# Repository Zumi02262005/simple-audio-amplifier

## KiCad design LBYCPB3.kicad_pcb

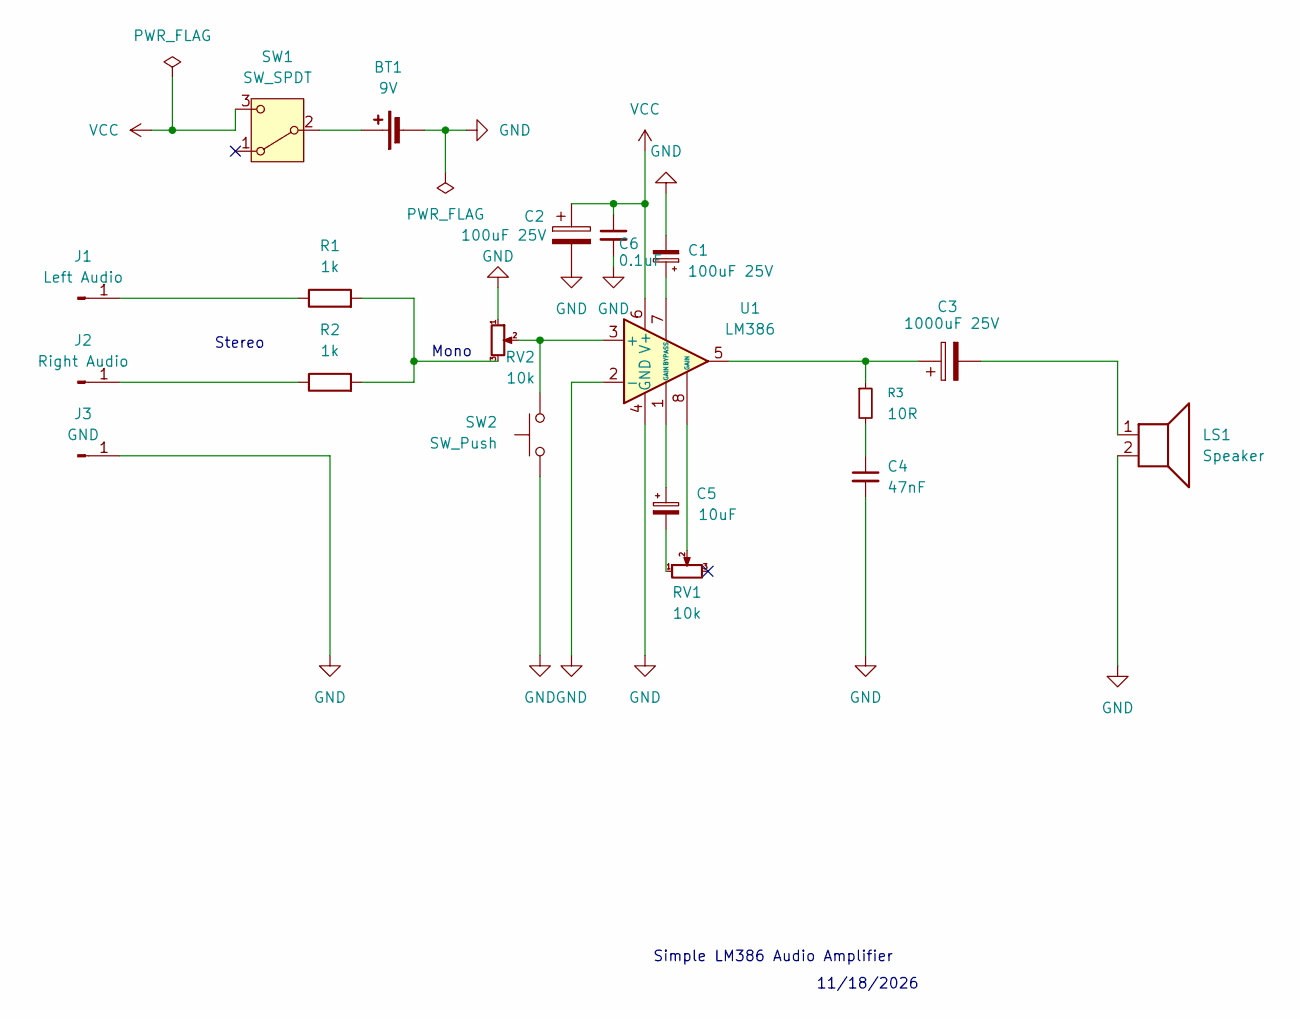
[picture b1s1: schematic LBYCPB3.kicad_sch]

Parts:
BT1: 9V; TerminalBlock_Phoenix_MKDS-1,5-2-5.08_1x02_P5.08mm_Horizont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
C1, C2: 100uF 25V; CP_Radial_D6.3mm_P2.50mm
C3: 1000uF 25V; CP_Radial_D10.0mm_P5.00mm
C4: 47nF; C_Disc_D5.0mm_W2.5mm_P5.00mm
C5: 10uF; CP_Radial_D5.0mm_P2.00mm
C6: 0.1uF; C_Disc_D5.0mm_W2.5mm_P5.00mm
J1: Left Audio; PinHeader_1x01_P2.54mm_Vertical
J2: Right Audio; PinHeader_1x01_P2.54mm_Vertical
J3: GND; PinHeader_1x01_P2.54mm_Vertical
LS1: Speaker; TerminalBlock_Phoenix_MKDS-1,5-2-5.08_1x02_P5.08mm_Horizont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
R1, R2: 1k; R_Axial_DIN0207_L6.3mm_D2.5mm_P7.62mm_Horizontal
R3: 10R; R_Axial_DIN0207_L6.3mm_D2.5mm_P7.62mm_Horizontal
RV1: 10k; Potentiometer_Bourns_3386P_Vertical
RV2: 10k; Potentiometer_Alps_RK09K_Single_Vertical
SW1: SW_SPDT; SW_Slide_SPDT_Straight_CK_OS102011MS2Q
SW2: SW_Push; SW_PUSH_6mm
U1: LM386; DIP-8_W7.62mm

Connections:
GND: BT1.2 (-), C1.2, C2.2, C4.2, C6.2, J3.1 (Pin_1_1), LS1.2, RV2.1, SW2.1, U1.2 (-), U1.4 (GND)
unnamed: BT1.1 (+), SW1.2 (B)
unnamed: C3.1, R3.1, U1.5
unnamed: C3.2, LS1.1
unnamed: C4.1, R3.2
unnamed: C5.1, U1.1 (GAIN)
unnamed: C5.2, RV1.1
unnamed: J1.1 (Pin_1_1), R1.1
unnamed: J2.1 (Pin_1_1), R2.1
unnamed: R1.2, R2.2, RV2.3
unnamed: RV1.2, U1.8 (GAIN)
unnamed: RV2.2, SW2.2, U1.3 (+)
unnamed: C1.1, U1.7 (BYPASS)
VCC: C2.1, C6.1, SW1.3 (C), U1.6 (V+)

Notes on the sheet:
11/18/2026
Simple LM386 Audio Amplifier
Mono
Stereo

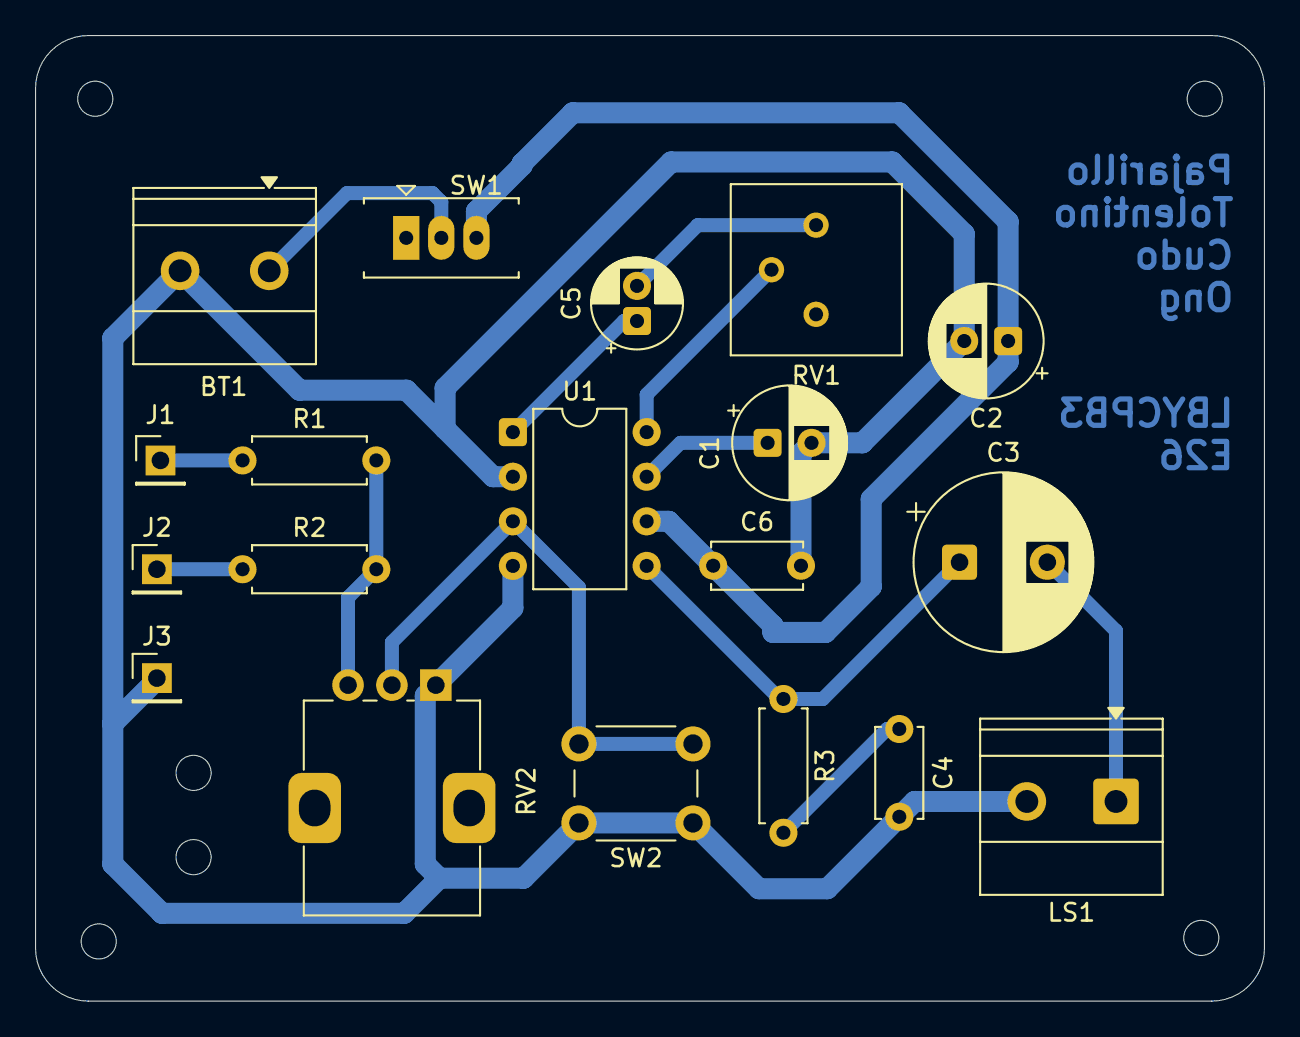
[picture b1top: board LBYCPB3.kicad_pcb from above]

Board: 2 copper layers, 70.0 x 55.0 mm, 19 parts (0 on the bottom side), 14 nets.
